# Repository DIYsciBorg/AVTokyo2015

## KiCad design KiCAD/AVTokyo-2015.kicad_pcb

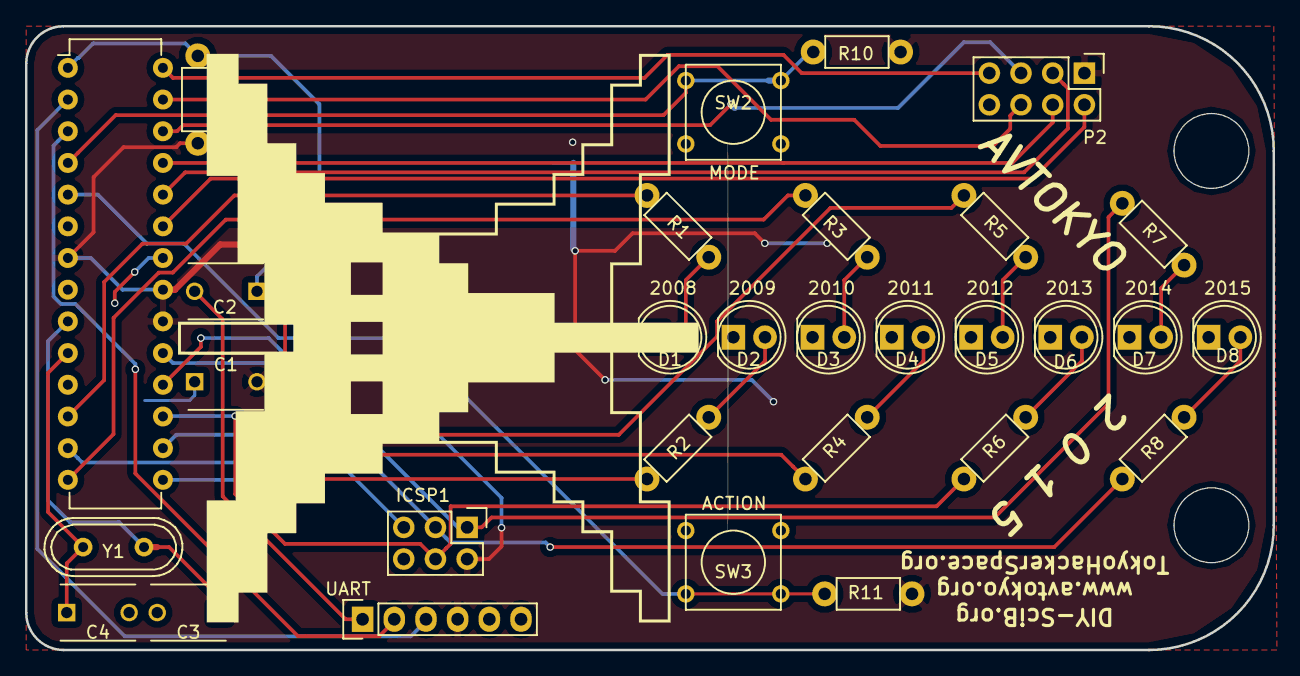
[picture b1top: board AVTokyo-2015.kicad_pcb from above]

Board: 2 copper layers, 100.0 x 50.0 mm, 31 parts (1 on the bottom side), 32 nets.

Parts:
BT1: CR2032 Bat; Battery_Holder_20mm_CR2032_BK883
C1, C2: 0.1uF; C_Disc_D6_P5
C3, C4: 22pF; C_Disc_D6_P5
D1: 2008; LED-5MM
D2: 2009; LED-5MM
D3: 2010; LED-5MM
D4: 2011; LED-5MM
D5: 2012; LED-5MM
D6: 2013; LED-5MM
D7: 2014; LED-5MM
D8: 2015; LED-5MM
IC1: ATMEGA328-P; DIP-28_W7.62mm
ICSP1: Pin_Header_Straight_2x03
P1: UART; Pin_Header_Straight_1x06
P2: CONN_02X04; Pin_Header_Straight_2x04
R1, R2, R3, R4, R5, R6, R7, R8: 470; resistor_7mm_8thWatt
R9, R10, R11: 10K; resistor_7mm_8thWatt
SW2: MODE; SW_PUSH_SMALL
SW3: ACTION; SW_PUSH_SMALL
Y1: Crystal_HC49-U_Vertical

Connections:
A0: IC1.23, P2.2
A1: IC1.24, P2.3
A2: IC1.25, P2.4
A3: IC1.26, P2.5
A4: IC1.27, P2.6
A5: IC1.28, P2.7
D2: IC1.4, R10.1, SW2.1
D3: IC1.5, R11.1, SW3.1
D6: IC1.12, R1.2
D7: IC1.13, R2.2
D8: IC1.14, R3.2
D9: IC1.15, R4.2
D10: IC1.16, R5.2
D11: IC1.17, ICSP1.4, R6.2
D12: IC1.18, ICSP1.1, R7.2
D13: IC1.19, ICSP1.3, R8.2
DTR: C2.2, P1.1
GND: BT1.2, C1.1, C3.2, C4.2, D1.1, D2.1, D3.1, D4.1, D5.1, D6.1, D7.1, D8.1, IC1.8, IC1.22, ICSP1.6, P1.6, P2.8, SW2.2, SW3.2
unnamed: C3.1, IC1.9, Y1.1
unnamed: C4.1, IC1.10, Y1.2
unnamed: D1.2, R1.1
unnamed: D2.2, R2.1
unnamed: D3.2, R3.1
unnamed: D4.2, R4.1
unnamed: D5.2, R5.1
unnamed: D6.2, R6.1
unnamed: D7.2, R7.1
unnamed: D8.2, R8.1
RESET: C2.1, IC1.1, ICSP1.5, R9.2
RXD: IC1.2, P1.3
TXD: IC1.3, P1.2
VCC: BT1.1, C1.2, IC1.7, IC1.20, IC1.21, ICSP1.2, P1.4, P2.1, R9.1, R10.2, R11.2

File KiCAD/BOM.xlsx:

|  | QTY to Build | 120
 |  |  | AKIZUKI |  |  | COSTS PER |  | PURCHASING
Qty | Reference | Description | Akizuki PN | Qty | Price | piece | board Cost | Pcs Req | Packs | expense
8 | D1, D2, D3, D4, D5, D6, D7, D8 | LED, Green, 5MM | I-03874 | 500 | 1900 | 3.8 | 30.4 | 960 | 1.92 | 3648
8 | R1, R2, R3, R4, R5, R6, R7, R8 | Resistor, 470 ohm | R-16471 | 100 | 100 | 1 | 8 | 960 | 9.6 | 960
3 | R9, R10, R11 | Resistor, 10K | R-16103 | 100 | 100 | 1 | 3 | 360 | 3.6 | 360
1 | IC1 | AT-MEGA328P-PU | I-03142 | 1 | 250 | 250 | 250 | 120 | 120 | 30000
1 | BT1 | CR-2032 Battery holder BK883 | P-06925 | 1 | 50 | 50 | 50 | 120 | 120 | 6000
2 | C1, C2 | Capacitor, 0.1uF | P-02181 | 500 | 2400 | 4.8 | 9.6 | 240 | 1 | 2400
2 | C3, C4 | Capacitor, 22pF | P-04151 | 500 | 1400 | 2.8 | 5.6 | 240 | 1 | 1400
1 | Y1 | Crystal, HC49, 16Mhz | P-08671 | 1 | 30 | 30 | 30 | 120 | 120 | 3600
1 | SW2 | Pushbutton RED | P-03646 | 1 | 10 | 10 | 10 | 120 | 120 | 1200
1 | SW3 | Pushbutton BLUE | P-03649 | 1 | 10 | 10 | 10 | 120 | 120 | 1200
1 | BATTERY | CR2032 | B-05694 | 5 | 200 | 40 | 40 | 120 | 24 | 4800
 |  |  |  |  |  |  | 446.6 |  |  | 55568

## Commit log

2015-10-27 :octocat: Added .gitattributes & .gitignore files
2015-10-27 initial
    PCB files, BOM and simple demo code
2015-10-27 cleanup and docs
